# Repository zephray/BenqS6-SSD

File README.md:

# BenqS6-SSD

Replacement SSD for Benq S6

Controller: SM2258XT
Flash: BGA 152pin Flash, up to 2 channel 8 CE
Interface: PATA UDMA up to 150 MB/s (if host supports)

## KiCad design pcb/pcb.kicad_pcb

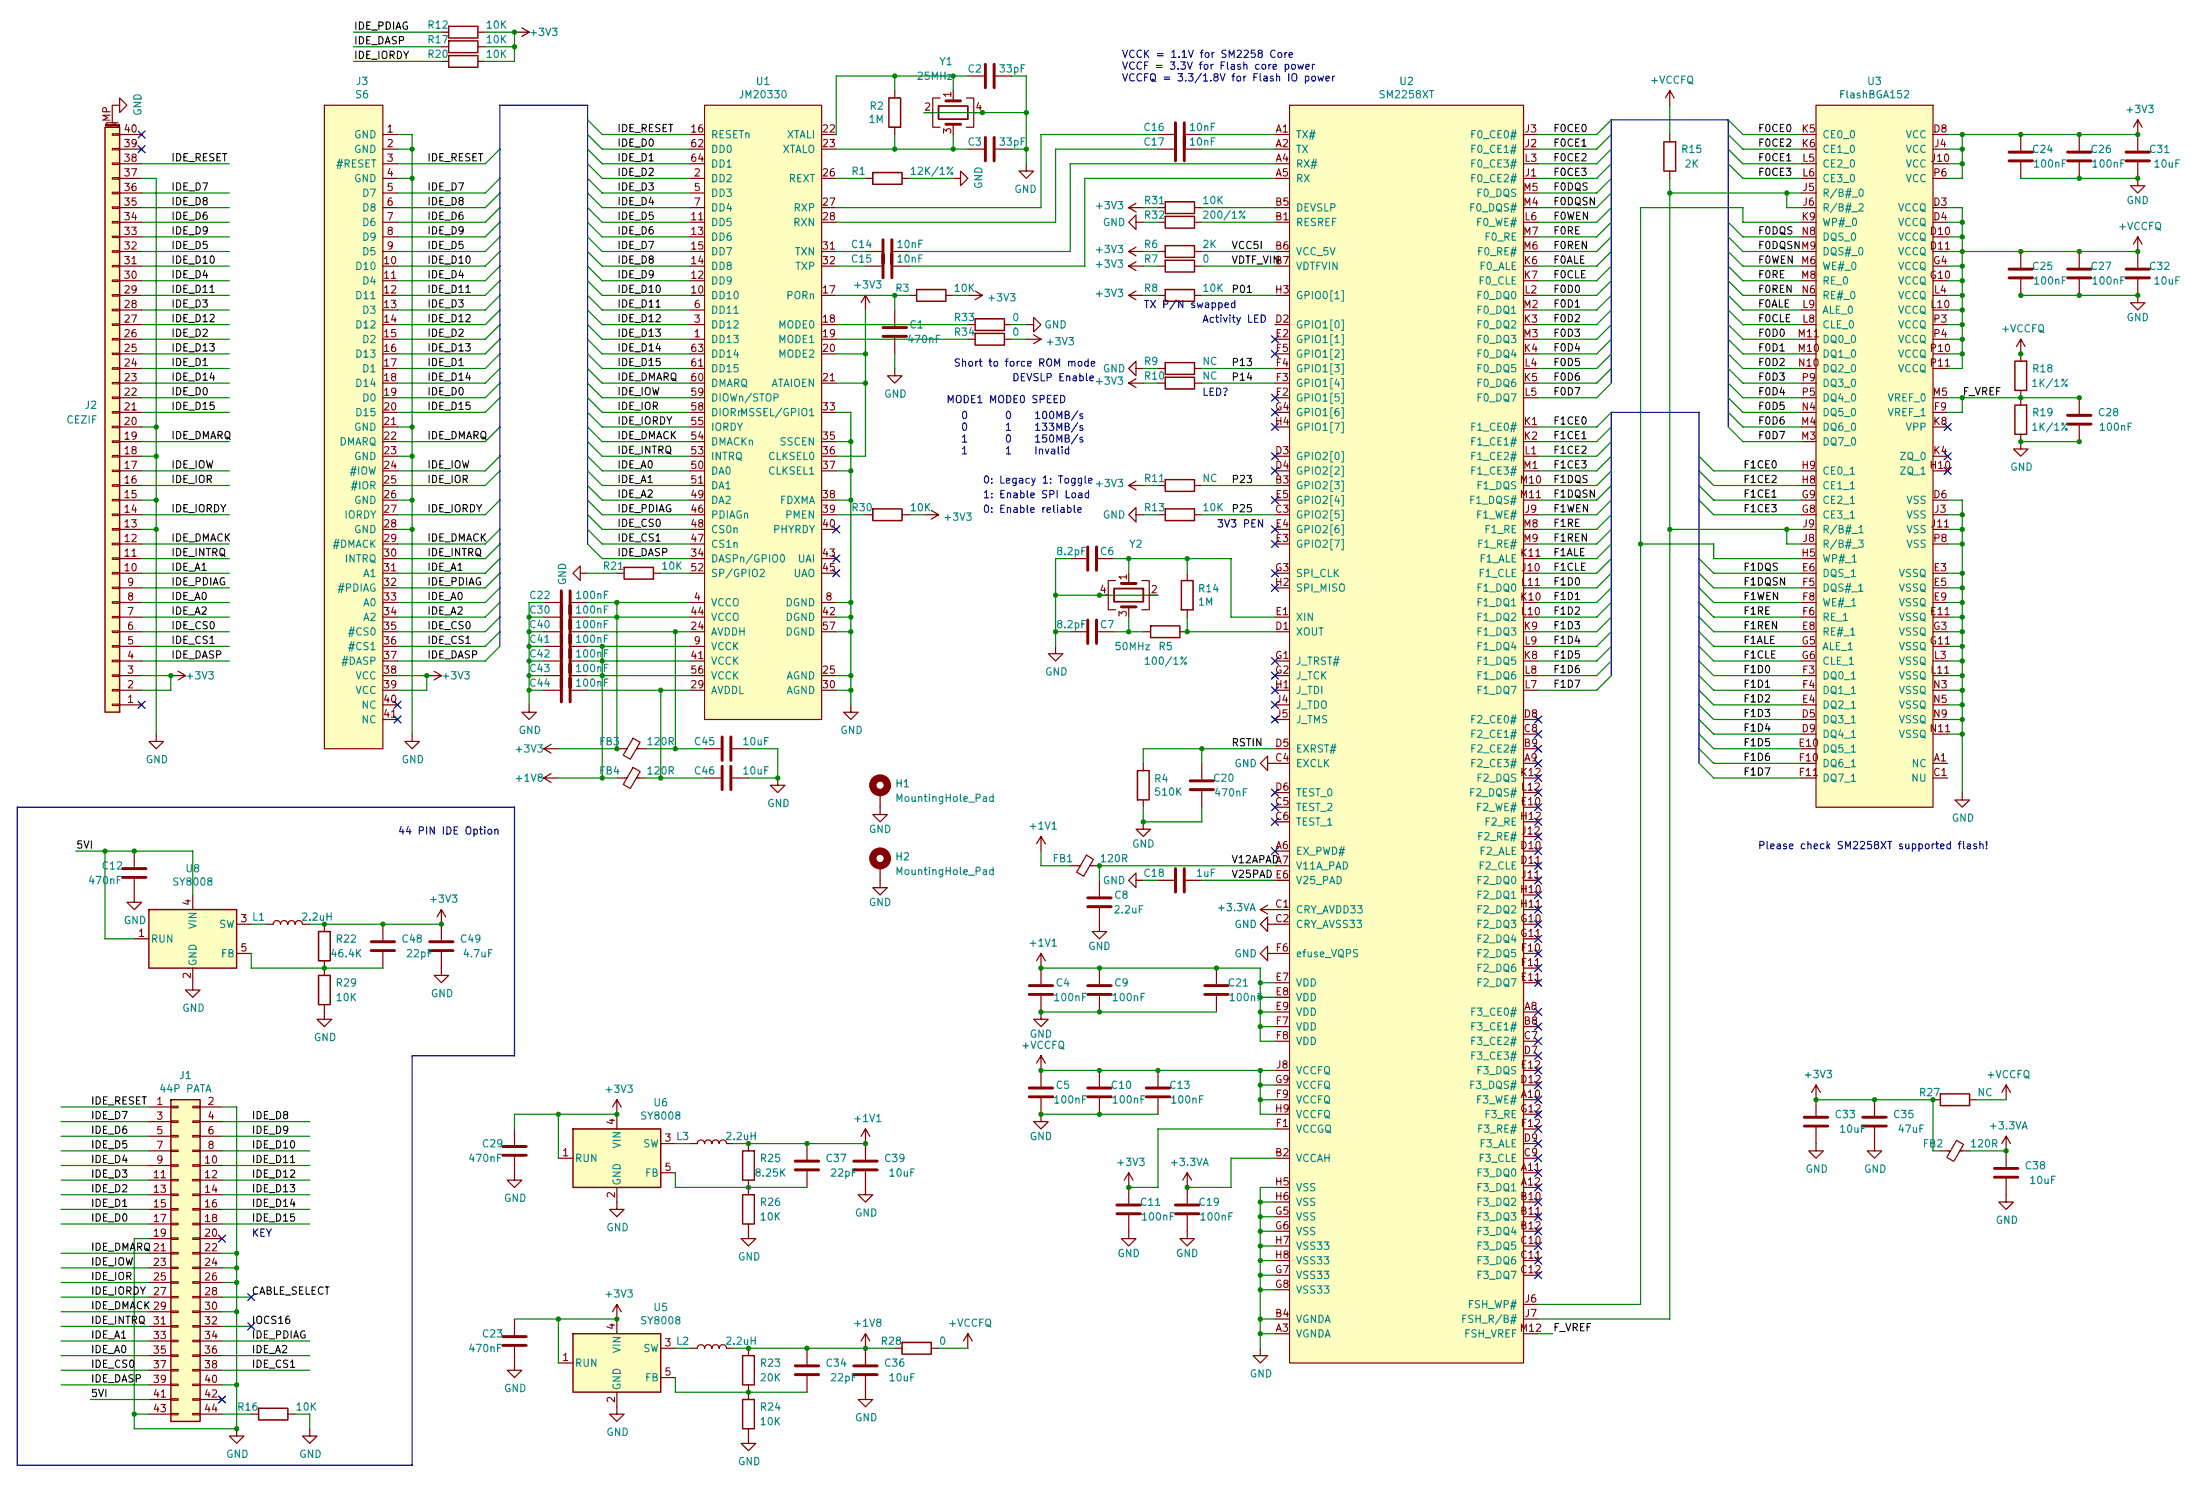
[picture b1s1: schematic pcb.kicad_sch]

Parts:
C1, C12, C20, C23, C29: 470nF; C_0402_1005Metric
C2, C3: 33pF; C_0402_1005Metric
C4, C5, C9, C10, C11, C13, C19, C21, C22, C24, C25, C26, C27, C28, C30, C40, C41, C42, C43, C44: 100nF; C_0402_1005Metric
C6, C7: 8.2pF; C_0402_1005Metric
C8: 2.2uF; C_0402_1005Metric
C14, C15, C16, C17: 10nF; C_0402_1005Metric
C18: 1uF; C_0402_1005Metric
C31, C32, C33, C36, C38, C39, C45, C46: 10uF; C_0402_1005Metric
C34, C37, C48: 22pF; C_0402_1005Metric
C35: 47uF; C_0805_2012Metric
C49: 4.7uF; C_0402_1005Metric
FB1, FB2, FB3, FB4: 120R; L_0603_1608Metric
H1, H2: MountingHole_Pad; MountingHole_2.2mm_M2_Pad_Via
J1: 44P PATA; PinHeader_2x22_P2.00mm_Vertical
J2: CEZIF; Hirose_FH12-40S-0.5SH_1x40-1MP_P0.50mm_Horizontal
J3: S6; FH35C-41S-0.3SHW
L1, L2, L3: 2.2uH; L_Vishay_IHLP-1212
R1: 12K/1%; R_0402_1005Metric
R2, R14: 1M; R_0402_1005Metric
R3, R8, R12, R13, R16, R17, R20, R21, R24, R26, R29, R30, R31: 10K; R_0402_1005Metric
R4: 510K; R_0402_1005Metric
R5: 100/1%; R_0402_1005Metric
R6, R15: 2K; R_0402_1005Metric
R7, R28, R33, R34: 0; R_0402_1005Metric
R9, R10, R11, R27: NC; R_0402_1005Metric
R18, R19: 1K/1%; R_0402_1005Metric
R22: 46.4K; R_0402_1005Metric
R23: 20K; R_0402_1005Metric
R25: 8.25K; R_0402_1005Metric
R32: 200/1%; R_0402_1005Metric
U1: JM20330; LQFP-64_10x10mm_P0.5mm
U2: SM2258XT; BGA-144_12x12_9.0x9.0mm
U3: FlashBGA152; BGA-152_14x18mm_Layout13x17_P0.5mm
U5, U6, U8: SY8008; TSOT-23-5
Y1: 25MHz; Oscillator_SMD_Abracon_ASE-4Pin_3.2x2.5mm
Y2: 50MHz; Oscillator_SMD_Abracon_ASE-4Pin_3.2x2.5mm

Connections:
+1V1: C4.2, C9.2, C21.2, C37.2, C39.2, FB1.2, L3.2, R25.2, U2.E7 (VDD), U2.E8 (VDD), U2.E9 (VDD), U2.F7 (VDD), U2.F8 (VDD)
+1V8: C34.2, C36.2, C41.2, C42.2, C43.2, FB4.2, L2.2, R23.2, R28.2, U1.9 (VCCK), U1.41 (VCCK), U1.56 (VCCK)
+3.3VA: C19.2, C38.2, FB2.1, U2.B2 (VCCAH), U2.C1 (CRY_AVDD33)
+3V3: C11.2, C22.2, C23.2, C24.2, C26.2, C29.2, C30.2, C31.2, C33.2, C35.2, C48.2, C49.2, FB2.2, FB3.2, J2.2, J2.3, J3.38 (VCC), J3.39 (VCC), L1.2, R3.1, R6.2, R7.2, R8.2, R10.2, R11.2, R12.1, R17.1, R20.1, R22.2, R27.2, R30.1, R31.2, R34.1, U1.4 (VCCO), U1.20 (MODE2), U1.21 (ATAIOEN), U1.36 (CLKSEL0), U1.44 (VCCO), U2.F1 (VCCGQ), U3.D8 (VCC), U3.J4 (VCC), U3.J10 (VCC), U3.P6 (VCC), U5.1 (RUN), U5.4 (VIN), U6.1 (RUN), U6.4 (VIN)
+VCCFQ: C5.2, C10.2, C13.2, C25.2, C27.2, C32.2, R15.2, R18.2, R27.1, R28.1, U2.F9 (VCCFQ), U2.G9 (VCCFQ), U2.H9 (VCCFQ), U2.J8 (VCCFQ), U3.C2 (NU), U3.D3 (VCCQ), U3.D4 (VCCQ), U3.D10 (VCCQ), U3.D11 (VCCQ), U3.G4 (VCCQ), U3.G10 (VCCQ), U3.L4 (VCCQ), U3.L10 (VCCQ), U3.P3 (VCCQ), U3.P4 (VCCQ), U3.P10 (VCCQ), U3.P11 (VCCQ)
/F0ALE: U2.K6 (F0_ALE), U3.L9 (ALE_0)
/F0CE0: U2.J3 (F0_CE0#), U3.K5 (CE0_0)
/F0CE1: U2.J2 (F0_CE1#), U3.L5 (CE2_0)
/F0CE2: U2.L3 (F0_CE3#), U3.K6 (CE1_0)
/F0CE3: U2.J1 (F0_CE2#), U3.L6 (CE3_0)
/F0CLE: U2.K7 (F0_CLE), U3.L8 (CLE_0)
/F0D0: U2.L2 (F0_DQ0), U3.M11 (DQ0_0)
/F0D1: U2.M2 (F0_DQ1), U3.M10 (DQ1_0)
/F0D2: U2.K3 (F0_DQ2), U3.N10 (DQ2_0)
/F0D3: U2.M3 (F0_DQ3), U3.P9 (DQ3_0)
/F0D4: U2.K4 (F0_DQ4), U3.P5 (DQ4_0)
/F0D5: U2.L4 (F0_DQ5), U3.N4 (DQ5_0)
/F0D6: U2.K5 (F0_DQ6), U3.M4 (DQ6_0)
/F0D7: U2.L5 (F0_DQ7), U3.M3 (DQ7_0)
/F0DQS: U2.M5 (F0_DQS), U3.N8 (DQS_0)
/F0DQSN: U2.M4 (F0_DQS#), U3.M9 (DQS#_0)
/F0RE: U2.M7 (F0_RE), U3.M8 (RE_0)
/F0REN: U2.M6 (F0_RE#), U3.N6 (RE#_0)
/F0WEN: U2.L6 (F0_WE#), U3.M6 (WE#_0)
/F1ALE: U2.K11 (F1_ALE), U3.G5 (ALE_1)
/F1CE0: U2.K1 (F1_CE0#), U3.H9 (CE0_1)
/F1CE1: U2.K2 (F1_CE1#), U3.G9 (CE2_1)
/F1CE2: U2.L1 (F1_CE2#), U3.H8 (CE1_1)
/F1CE3: U2.M1 (F1_CE3#), U3.G8 (CE3_1)
/F1CLE: U2.J10 (F1_CLE), U3.G6 (CLE_1)
/F1D0: U2.L11 (F1_DQ0), U3.F3 (DQ0_1)
/F1D1: U2.K10 (F1_DQ1), U3.F4 (DQ1_1)
/F1D2: U2.L10 (F1_DQ2), U3.E4 (DQ2_1)
/F1D3: U2.K9 (F1_DQ3), U3.D5 (DQ3_1)
/F1D4: U2.L9 (F1_DQ4), U3.D9 (DQ4_1)
/F1D5: U2.K8 (F1_DQ5), U3.E10 (DQ5_1)
/F1D6: U2.L8 (F1_DQ6), U3.F10 (DQ6_1)
/F1D7: U2.L7 (F1_DQ7), U3.F11 (DQ7_1)
/F1DQS: U2.M10 (F1_DQS), U3.E6 (DQS_1)
/F1DQSN: U2.M11 (F1_DQS#), U3.F5 (DQS#_1)
/F1RE: U2.M8 (F1_RE), U3.F6 (RE_1)
/F1REN: U2.M9 (F1_RE#), U3.E8 (RE#_1)
/F1WEN: U2.J9 (F1_WE#), U3.F8 (WE#_1)
/F_VREF: C28.2, R18.1, R19.2, U2.M12 (FSH_VREF), U3.B1 (NC), U3.D1 (NU), U3.F9 (VREF_1), U3.M5 (VREF_0)
/IDE_A0: J1.35, J2.8, J3.33 (A0), U1.50 (DA0)
/IDE_A1: J1.33, J2.10, J3.31 (A1), U1.51 (DA1)
/IDE_A2: J1.36, J2.7, J3.34 (A2), U1.49 (DA2)
/IDE_CS0: J1.37, J2.6, J3.35 (#CS0), U1.48 (CS0n)
/IDE_CS1: J1.38, J2.5, J3.36 (#CS1), U1.47 (CS1n)
/IDE_D0: J1.17, J2.22, J3.19 (D0), U1.62 (DD0)
/IDE_D1: J1.15, J2.24, J3.17 (D1), U1.64 (DD1)
/IDE_D2: J1.13, J2.26, J3.15 (D2), U1.2 (DD2)
/IDE_D3: J1.11, J2.28, J3.13 (D3), U1.5 (DD3)
/IDE_D4: J1.9, J2.30, J3.11 (D4), U1.7 (DD4)
/IDE_D5: J1.7, J2.32, J3.9 (D5), U1.11 (DD5)
/IDE_D6: J1.5, J2.34, J3.7 (D6), U1.13 (DD6)
/IDE_D7: J1.3, J2.36, J3.5 (D7), U1.15 (DD7)
/IDE_D8: J1.4, J2.35, J3.6 (D8), U1.14 (DD8)
/IDE_D9: J1.6, J2.33, J3.8 (D9), U1.12 (DD9)
/IDE_D10: J1.8, J2.31, J3.10 (D10), U1.10 (DD10)
/IDE_D11: J1.10, J2.29, J3.12 (D11), U1.6 (DD11)
/IDE_D12: J1.12, J2.27, J3.14 (D12), U1.3 (DD12)
/IDE_D13: J1.14, J2.25, J3.16 (D13), U1.1 (DD13)
/IDE_D14: J1.16, J2.23, J3.18 (D14), U1.63 (DD14)
/IDE_D15: J1.18, J2.21, J3.20 (D15), U1.61 (DD15)
/IDE_DASP: J1.39, J2.4, J3.37 (#DASP), R17.2, U1.34 (DASPn/GPIO0)
/IDE_DMACK: J1.29, J2.12, J3.29 (#DMACK), U1.54 (DMACKn)
/IDE_DMARQ: J1.21, J2.19, J3.22 (DMARQ), U1.60 (DMARQ)
/IDE_INTRQ: J1.31, J2.11, J3.30 (INTRQ), U1.53 (INTRQ)
/IDE_IOR: J1.25, J2.16, J3.25 (#IOR), U1.58 (DIORn)
/IDE_IORDY: J1.27, J2.14, J3.27 (IORDY), R20.2, U1.55 (IORDY)
/IDE_IOW: J1.23, J2.17, J3.24 (#IOW), U1.59 (DIOWn/STOP)
/IDE_PDIAG: J1.34, J2.9, J3.32 (#PDIAG), R12.2, U1.46 (PDIAGn)
/IDE_RESET: J1.1, J2.38, J3.3 (#RESET), U1.16 (RESETn)
/P01: R8.1, U2.H3 (GPIO0[1])
/P13: R9.1, U2.F4 (GPIO1[3])
/P14: R10.1, U2.F3 (GPIO1[4])
/P23: R11.1, U2.B3 (GPIO2[3])
/P25: R13.1, U2.C3 (GPIO2[5])
/RSTIN: C20.2, R4.1, U2.D5 (EXRST#)
/V12APAD: C8.2, FB1.1, U2.A7 (V11A_PAD)
/V25PAD: C18.2, U2.E6 (V25_PAD)
/VCC5I: R6.1, U2.B6 (VCC_5V)
/VDTF_VIN: R7.1, U2.B7 (VDTFVIN)
GND: C1.1, C2.2, C3.2, C4.1, C5.1, C6.2, C7.2, C8.1, C9.1, C10.1, C11.1, C12.1, C13.1, C18.1, C19.1, C20.1, C21.1, C22.1, C23.1, C24.1, C25.1, C26.1, C27.1, C28.1, C29.1, C30.1, C31.1, C32.1, C33.1, C35.1, C36.1, C38.1, C39.1, C40.1, C41.1, C42.1, C43.1, C44.1, C45.1, C46.1, C49.1, H1.1, H2.1, J1.2, J1.19, J1.22, J1.24, J1.26, J1.30, J1.40, J1.43, J2.13, J2.15, J2.18, J2.20, J2.37, J2.MP (MountPin), J3.1 (GND), J3.2 (GND), J3.4 (GND), J3.21 (GND), J3.23 (GND), J3.26 (GND), J3.28 (GND), R1.1, R4.2, R9.2, R13.2, R16.1, R19.1, R21.2, R24.1, R26.1, R29.1, R32.2, R33.1, U1.8 (DGND), U1.25 (AGND), U1.30 (AGND), U1.33 (MSSEL/GPIO1), U1.35 (SSCEN), U1.37 (CLKSEL1), U1.38 (FDXMA), U1.42 (DGND), U1.57 (DGND), U2.A3 (VGNDA), U2.B4 (VGNDA), U2.C2 (CRY_AVSS33), U2.C4 (EXCLK), U2.F6 (efuse_VQPS), U2.G5 (VSS), U2.G6 (VSS), U2.G7 (VSS33), U2.G8 (VSS33), U2.H5 (VSS), U2.H6 (VSS), U2.H7 (VSS33), U2.H8 (VSS33), U3.A10 (NC), U3.B12 (NC), U3.C10 (NU), U3.D2 (NU), U3.D6 (VSS), U3.E3 (VSSQ), U3.E5 (VSSQ), U3.E9 (VSSQ), U3.E11 (VSSQ), U3.G3 (VSSQ), U3.G11 (VSSQ), U3.J3 (VSS), U3.J11 (VSS), U3.L3 (VSSQ), U3.L11 (VSSQ), U3.N3 (VSSQ), U3.N5 (VSSQ), U3.N9 (VSSQ), U3.N11 (VSSQ), U3.P8 (VSS), U5.2 (GND), U6.2 (GND), U8.2 (GND), Y1.2, Y1.4, Y2.2, Y2.4
unnamed: C1.2, R3.2, U1.17 (PORn)
unnamed: C2.1, R2.1, U1.22 (XTALI), Y1.1
unnamed: C3.1, R2.2, U1.23 (XTALO), Y1.3
unnamed: C6.1, R14.1, U2.E1 (XIN), Y2.1
unnamed: C7.1, R5.2, Y2.3
unnamed: C12.2, J1.41, U8.1 (RUN), U8.4 (VIN)
unnamed: C14.1, U1.31 (TXN)
unnamed: C14.2, U2.A4 (RX#)
unnamed: C15.1, U1.32 (TXP)
unnamed: C15.2, U2.A5 (RX)
unnamed: C16.1, U1.27 (RXP)
unnamed: C16.2, U2.A1 (TX#)
unnamed: C17.1, U1.28 (RXN)
unnamed: C17.2, U2.A2 (TX)
unnamed: C34.1, R23.1, R24.2, U5.5 (FB)
unnamed: C37.1, R25.1, R26.2, U6.5 (FB)
unnamed: C40.2, C45.2, FB3.1, U1.24 (AVDDH)
unnamed: C44.2, C46.2, FB4.1, U1.29 (AVDDL)
unnamed: C48.1, R22.1, R29.2, U8.5 (FB)
unnamed: J1.44, R16.2
unnamed: L1.1, U8.3 (SW)
unnamed: L2.1, U5.3 (SW)
unnamed: L3.1, U6.3 (SW)
unnamed: R1.2, U1.26 (REXT)
unnamed: R5.1, R14.2, U2.D1 (XOUT)
unnamed: R15.1, U2.J7 (FSH_R/B#), U3.J5 (R/B#_0), U3.J6 (R/B#_2), U3.J8 (R/B#_3), U3.J9 (R/B#_1)
unnamed: R21.1, U1.52 (SP/GPIO2)
unnamed: R30.2, U1.39 (PMEN)
unnamed: R31.1, U2.B5 (DEVSLP)
unnamed: R32.1, U2.B1 (RESREF)
unnamed: R33.2, U1.18 (MODE0)
unnamed: R34.2, U1.19 (MODE1)
unnamed: U2.J6 (FSH_WP#), U3.H5 (WP#_1), U3.K9 (WP#_0)

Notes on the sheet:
0 0 1 1
Please check SM2258XT supported flash!
1: Enable SPI Load
3V3 PEN
TX P/N swapped
LED?
0 1 0 1
Activity LED
MODE1 MODE0 SPEED
Short to force ROM mode
0: Enable reliable
100MB/s 133MB/s 150MB/s Invalid
KEY
VCCK = 1.1V for SM2258 Core VCCF = 3.3V for Flash core power VCCFQ = 3.3/1.8V for Flash IO power
44 PIN IDE Option
DEVSLP Enable
0: Legacy 1: Toggle

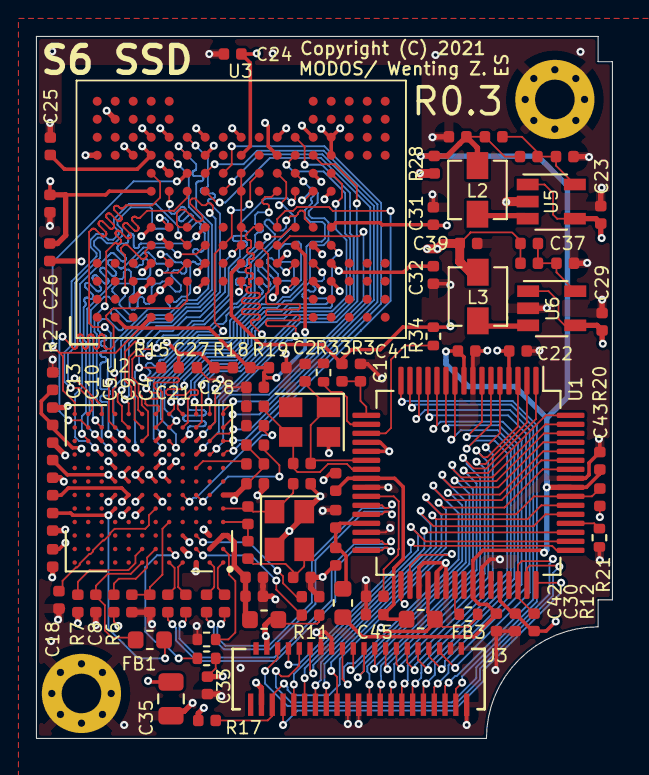
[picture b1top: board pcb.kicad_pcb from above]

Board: 4 copper layers, 32.0 x 39.0 mm, 92 parts (0 on the bottom side), 114 nets.

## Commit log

2020-10-25 Schematics first revision
2020-10-31 Working on layout
2020-11-04 First revision freeze
2021-11-19 Upgrade to 5.99, clean up
2021-11-28 Upgrade to new nightly, remove 5V charge pump, add UDMA speed option resistor
2021-12-24 Rev 0.3

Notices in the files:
pcb/pcb.kicad_pcb:
Copyright Wenting Zhang 2021
This device is Open Hardware and the
design source is licensed under the
CERN-OHL-P v2. You could download
Copyright (C) 2021
